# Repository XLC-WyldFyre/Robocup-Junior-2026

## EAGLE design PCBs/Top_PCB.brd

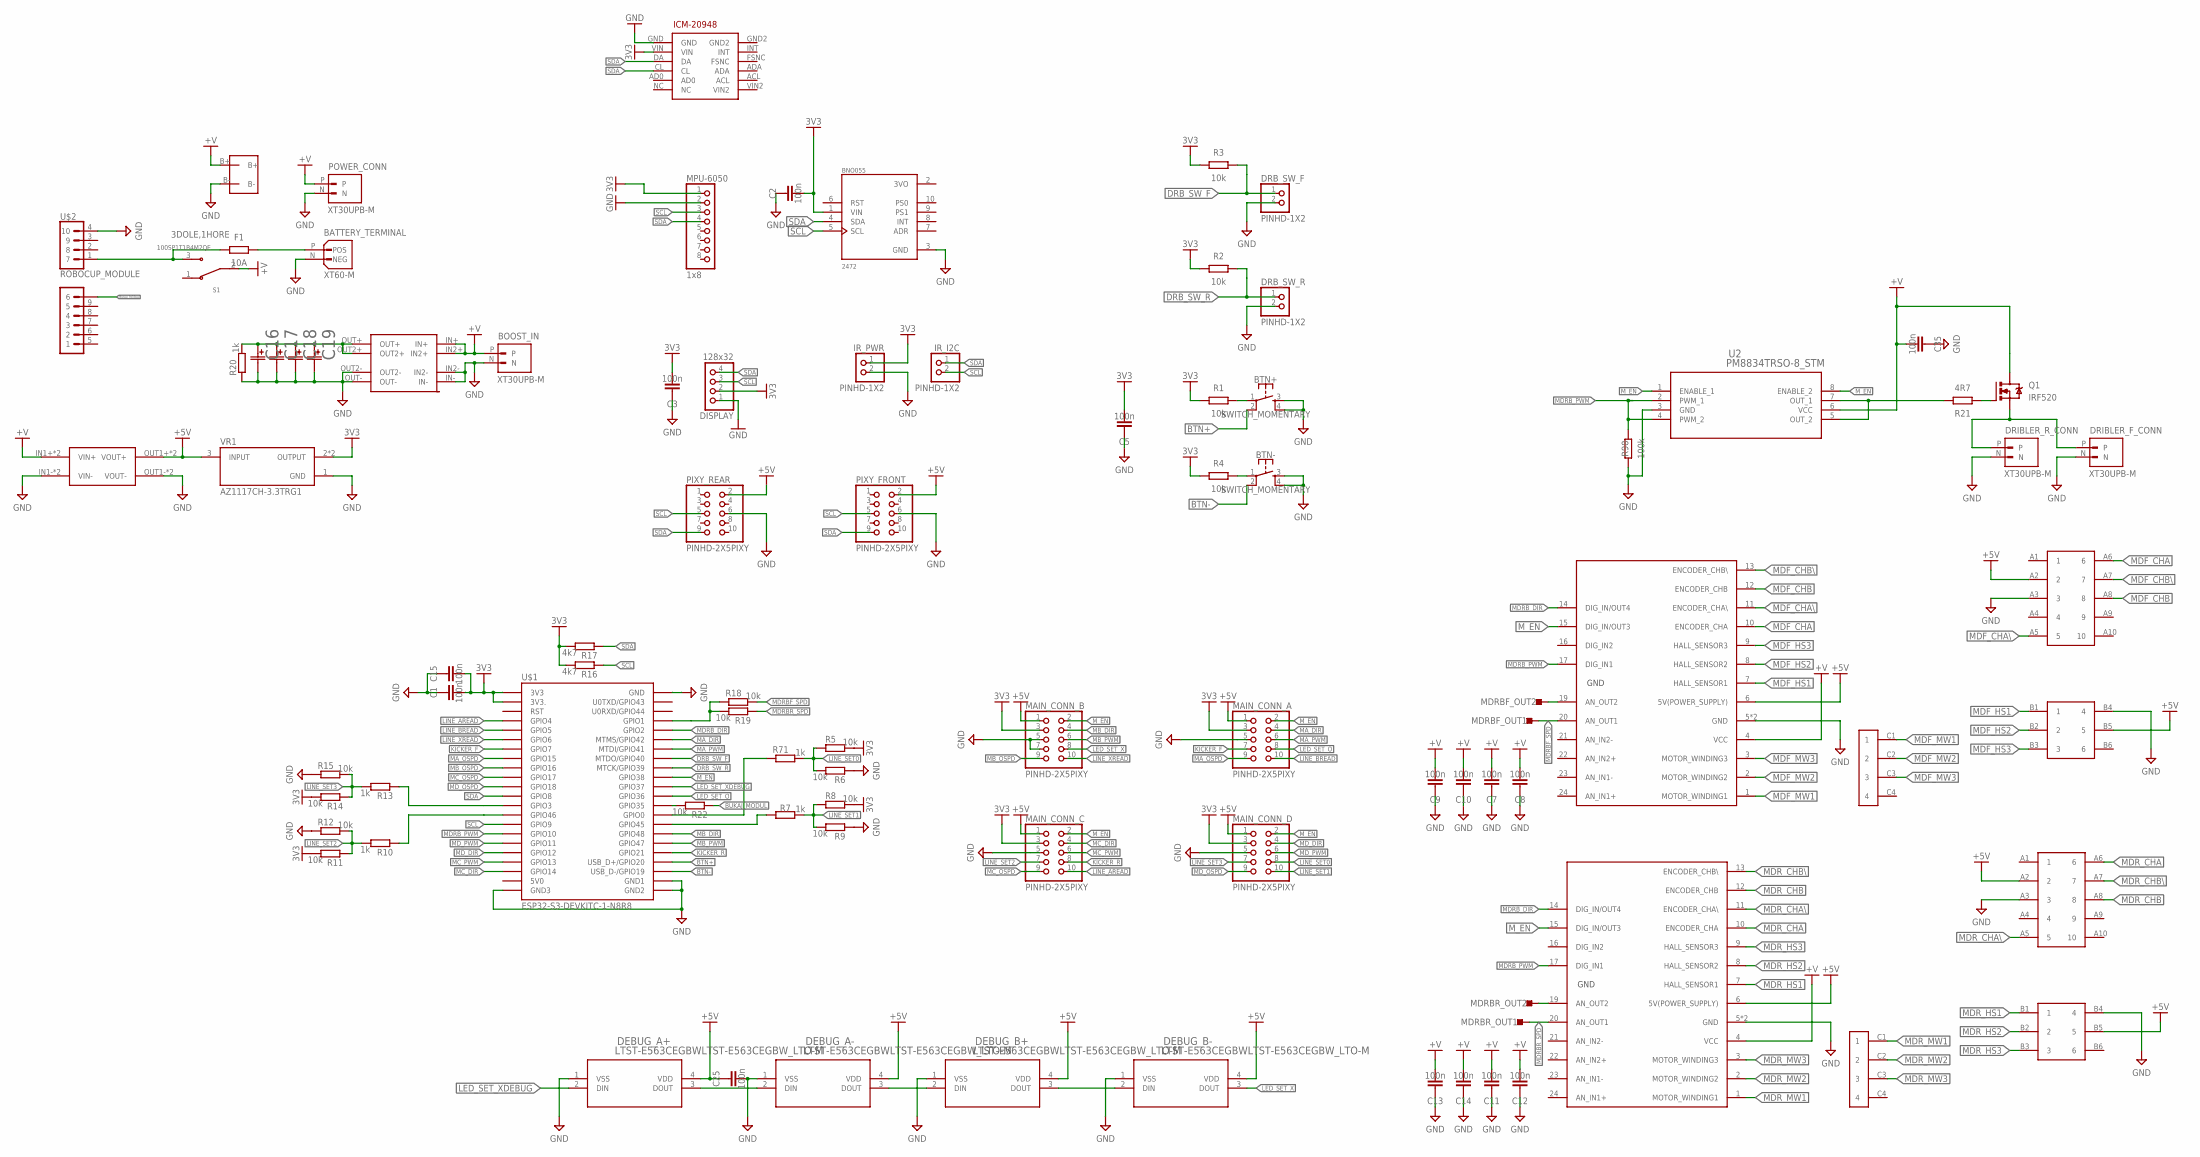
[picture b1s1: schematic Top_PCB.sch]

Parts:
BATTERY_TERMINAL: XT60-M; AMASS_XT60-M
BATT_VOLTAGE: BATT_V_METER; 1X02
BNO055: 2472; MODULE_2472
BOOST_IN: XT30UPB-M; AMASS_XT30UPB-M
BTN+: SWITCH_MOMENTARY; SWITCH-MOMENTARY-PTH-6.5MM
BTN-: SWITCH_MOMENTARY; SWITCH-MOMENTARY-PTH-6.5MM
C1, C2, C3, C5, C7, C8, C9, C10, C11, C12, C13, C14, C15, C25, C35: 100n; CAPC2012X110
C16, C17, C18, C19: 1mF; CAP_108CKE_ILC
DEBUG_A+: LTST-E563CEGBWLTST-E563CEGBW_LTO-M; LTST-E563CEGBW_LTO-M
DEBUG_A-: LTST-E563CEGBWLTST-E563CEGBW_LTO-M; LTST-E563CEGBW_LTO-M
DEBUG_B+: LTST-E563CEGBWLTST-E563CEGBW_LTO-M; LTST-E563CEGBW_LTO-M
DEBUG_B-: LTST-E563CEGBWLTST-E563CEGBW_LTO-M; LTST-E563CEGBW_LTO-M
DISPLAY: 128x32; 1X04
DRB_SW_F: PINHD-1X2; 1X02
DRB_SW_R: PINHD-1X2; 1X02
DRIBLER_F_CONN: XT30UPB-M; AMASS_XT30UPB-M
DRIBLER_R_CONN: XT30UPB-M; AMASS_XT30UPB-M
F1: 10A; RESC3216X70
ICM-20948: ICM-20948
IR_I2C: PINHD-1X2; 1X02
IR_PWR: PINHD-1X2; 1X02
MAIN_CONN_A: PINHD-2X5PIXY; 2X05
MAIN_CONN_B: PINHD-2X5PIXY; 2X05
MAIN_CONN_C: PINHD-2X5PIXY; 2X05
MAIN_CONN_D: PINHD-2X5PIXY; 2X05
MDRBF_OUT1, MDRBF_OUT2: TESTPOINT_TPS-PAD-036; TESTPOINT_PAD-036
MDRBR_OUT1, MDRBR_OUT2: TESTPOINT_TPS-PAD-036; TESTPOINT_PAD-036
MPU-6050: 1x8; 1X08
PIXY_FRONT: PINHD-2X5PIXY; 2X05
PIXY_REAR: PINHD-2X5PIXY; 2X05
POWER_CONN: XT30UPB-M; AMASS_XT30UPB-M
Q1: IRF520; TO220BV
R1, R2, R3, R4, R5, R6, R8, R9, R11, R12, R14, R15, R18, R19, R22: 10k; RESC2012X65
R7, R10, R13, R20, R71: 1k; RESC2012X65
R16, R17: 4k7; RESC2012X65
R21: 4R7; RESC2012X65
R98: 100k; RESC2012X65
S1: 100SP1T1B4M2QE; SW_100SP1T1B4M2QE
U2: PM8834TRSO-8_STM; SO-8_STM
U$1: ESP32-S3-DEVKITC-1-N8R8
U$2: ROBOCUP_MODULE
U$4: MP1584; DC-BRICK
U$5: BOOST
U$7, U$9: ESCON24/224/2; ESCON24/2
U$8, U$11: PIN2.54-2X5
U$10, U$12: MX-44914-0601
U$13, U$14: MX5566
VR1: AZ1117CH-3.3TRG1; VREG_AZ1117CH-3.3TRG1

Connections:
3DOLE,1HORE: F1.1, S1.3, U$2.1 (7)
3V3: BNO055.1 (VIN), C1.2, C2.2, C3.2, C5.2, C15.2, DISPLAY.2, ICM-20948.VIN, IR_PWR.1, MAIN_CONN_A.3, MAIN_CONN_B.3, MAIN_CONN_C.3, MAIN_CONN_D.3, MPU-6050.1, R1.1, R2.1, R3.1, R4.1, R5.1, R8.1, R11.1, R14.1, R16.1, R17.1, U$1.J1_1 (3V3), U$1.J1_2 (3V3.), VR1.2 (OUTPUT), VR1.4 (OUTPUT)
3VO: BNO055.2 (3VO)
5V0: U$1.J1_21 (5V0)
+5V: C25.1, DEBUG_A+.4 (VDD), DEBUG_A-.4 (VDD), DEBUG_B+.4 (VDD), DEBUG_B-.4 (VDD), MAIN_CONN_A.1, MAIN_CONN_B.1, MAIN_CONN_C.1, MAIN_CONN_D.1, PIXY_FRONT.2, PIXY_REAR.2, U$4.OUT1+ (VOUT+), U$4.OUT2+ (VOUT+), U$7.6 (5V(POWER_SUPPLY)), U$8.A2 (2), U$9.6 (5V(POWER_SUPPLY)), U$10.B5 (5), U$11.A2 (2), U$12.B5 (5), VR1.3 (INPUT)
+V: BATT_VOLTAGE.B+, BOOST_IN.P, C7.2, C8.2, C9.2, C10.2, C11.2, C12.2, C13.2, C14.2, C35.2, POWER_CONN.P, Q1.D, S1.2, U2.6 (VCC), U$4.IN1+ (VIN+), U$4.IN2+ (VIN+), U$5.IN2+, U$5.IN+, U$7.4 (VCC), U$9.4 (VCC)
BTN+: BTN+.2, U$1.J3_19 (USB_D+/GPIO20)
BTN-: BTN-.2, U$1.J3_20 (USB_D-/GPIO19)
BUKAJ_MODUL: R22.2, U$2.10 (6)
DRB_SW_F: DRB_SW_F.1, R3.2, U$1.J3_8 (MTDO/GPIO40)
DRB_SW_R: DRB_SW_R.1, R2.2, U$1.J3_9 (MTCK/GPIO39)
GND: BATTERY_TERMINAL.N (NEG), BATT_VOLTAGE.B-, BNO055.3 (GND), BOOST_IN.N, BTN+.3, BTN+.4, BTN-.3, BTN-.4, C1.1, C2.1, C3.1, C5.1, C7.1, C8.1, C9.1, C10.1, C11.1, C12.1, C13.1, C14.1, C15.1, C16.2, C17.2, C18.2, C19.2, C25.2, C35.1, DEBUG_A+.1 (VSS), DEBUG_A-.1 (VSS), DEBUG_B+.1 (VSS), DEBUG_B-.1 (VSS), DISPLAY.1, DRB_SW_F.2, DRB_SW_R.2, DRIBLER_F_CONN.N, DRIBLER_R_CONN.N, ICM-20948.GND, IR_PWR.2, MAIN_CONN_A.5, MAIN_CONN_B.5, MAIN_CONN_B.7, MAIN_CONN_C.5, MAIN_CONN_D.5, MPU-6050.2, PIXY_FRONT.6, PIXY_REAR.6, POWER_CONN.N, R6.2, R9.2, R12.2, R15.2, R20.2, R98.1, U2.3 (GND), U$1.J1_22 (GND3), U$1.J3_1 (GND), U$1.J3_21 (GND1), U$1.J3_22 (GND2), U$2.4 (10), U$4.IN1- (VIN-), U$4.IN2- (VIN-), U$4.OUT1- (VOUT-), U$4.OUT2- (VOUT-), U$5.IN2-, U$5.IN-, U$5.OUT2-, U$5.OUT-, U$7.5 (GND), U$7.18 (GND), U$8.A3 (3), U$9.5 (GND), U$9.18 (GND), U$10.B4 (4), U$11.A3 (3), U$12.B4 (4), VR1.1 (GND)
KICKER_F: MAIN_CONN_A.7, U$1.J1_7 (GPIO7)
KICKER_R: MAIN_CONN_C.8, U$1.J3_18 (GPIO21)
LED_SET_DEBUG1: DEBUG_A-.3 (DOUT), DEBUG_B+.2 (DIN)
LED_SET_O: MAIN_CONN_A.8, U$1.J3_12 (GPIO36)
LED_SET_X: DEBUG_B-.3 (DOUT), MAIN_CONN_B.8
LED_SET_XDEBUG: DEBUG_A+.2 (DIN), U$1.J3_11 (GPIO37)
LINE_AREAD: MAIN_CONN_C.10, U$1.J1_4 (GPIO4)
LINE_BREAD: MAIN_CONN_A.10, U$1.J1_5 (GPIO5)
LINE_SET0: MAIN_CONN_D.8, R5.2, R6.1, R71.1
LINE_SET1: MAIN_CONN_D.10, R7.1, R8.2, R9.1
LINE_SET2: MAIN_CONN_C.7, R10.1, R11.2, R12.1
LINE_SET3: MAIN_CONN_D.7, R13.1, R14.2, R15.1
LINE_XREAD: MAIN_CONN_B.10, U$1.J1_6 (GPIO6)
MA_DIR: MAIN_CONN_A.4, U$1.J3_6 (MTMS/GPIO42)
MA_OSPD: MAIN_CONN_A.9, U$1.J1_8 (GPIO15)
MA_PWM: MAIN_CONN_A.6, U$1.J3_7 (MTDI/GPIO41)
MB_DIR: MAIN_CONN_B.4, U$1.J3_16 (GPIO48)
MB_OSPD: MAIN_CONN_B.9, U$1.J1_9 (GPIO16)
MB_PWM: MAIN_CONN_B.6, U$1.J3_17 (GPIO47)
MC_DIR: MAIN_CONN_C.4, U$1.J1_20 (GPIO14)
MC_OSPD: MAIN_CONN_C.9, U$1.J1_10 (GPIO17)
MC_PWM: MAIN_CONN_C.6, U$1.J1_19 (GPIO13)
MDF_CHA: U$9.10 (ENCODER_CHA), U$11.A6 (6)
MDF_CHA\\: U$9.11 (ENCODER_CHA\\), U$11.A5 (5)
MDF_CHB: U$9.12 (ENCODER_CHB), U$11.A8 (8)
MDF_CHB\\: U$9.13 (ENCODER_CHB\\), U$11.A7 (7)
MDF_HS1: U$9.7 (HALL_SENSOR1), U$12.B1 (1)
MDF_HS2: U$9.8 (HALL_SENSOR2), U$12.B2 (2)
MDF_HS3: U$9.9 (HALL_SENSOR3), U$12.B3 (3)
MDF_MW1: U$9.1 (MOTOR_WINDING1), U$13.C1 (1)
MDF_MW2: U$9.2 (MOTOR_WINDING2), U$13.C2 (2)
MDF_MW3: U$9.3 (MOTOR_WINDING3), U$13.C3 (3)
MDRBF_SPD: MDRBF_OUT1.1, R18.1, U$9.20 (AN_OUT1)
MDRBR_SPD: MDRBR_OUT1.1, R19.2, U$7.20 (AN_OUT1)
MDRB_DIR: U$1.J3_5 (GPIO2), U$7.14 (DIG_IN/OUT4), U$9.14 (DIG_IN/OUT4)
MDRB_PWM: R98.2, U2.2 (PWM_1), U2.4 (PWM_2), U$1.J1_16 (GPIO10), U$7.17 (DIG_IN1), U$9.17 (DIG_IN1)
MDRB_SPD: R18.2, R19.1, U$1.J3_4 (GPIO1)
MDR_CHA: U$7.10 (ENCODER_CHA), U$8.A6 (6)
MDR_CHA\\: U$7.11 (ENCODER_CHA\\), U$8.A5 (5)
MDR_CHB: U$7.12 (ENCODER_CHB), U$8.A8 (8)
MDR_CHB\\: U$7.13 (ENCODER_CHB\\), U$8.A7 (7)
MDR_HS1: U$7.7 (HALL_SENSOR1), U$10.B1 (1)
MDR_HS2: U$7.8 (HALL_SENSOR2), U$10.B2 (2)
MDR_HS3: U$7.9 (HALL_SENSOR3), U$10.B3 (3)
MDR_MW1: U$7.1 (MOTOR_WINDING1), U$14.C1 (1)
MDR_MW2: U$7.2 (MOTOR_WINDING2), U$14.C2 (2)
MDR_MW3: U$7.3 (MOTOR_WINDING3), U$14.C3 (3)
MD_DIR: MAIN_CONN_D.4, U$1.J1_18 (GPIO12)
MD_OSPD: MAIN_CONN_D.9, U$1.J1_11 (GPIO18)
MD_PWM: MAIN_CONN_D.6, U$1.J1_17 (GPIO11)
M_EN: MAIN_CONN_A.2, MAIN_CONN_B.2, MAIN_CONN_C.2, MAIN_CONN_D.2, U2.1 (ENABLE_1), U2.8 (ENABLE_2), U$1.J3_10 (GPIO38), U$7.15 (DIG_IN/OUT3), U$9.15 (DIG_IN/OUT3)
unnamed: DEBUG_B+.3 (DOUT), DEBUG_B-.2 (DIN)
unnamed: C16.1, C17.1, C18.1, C19.1, R20.1, U$5.OUT2+, U$5.OUT+
unnamed: BATTERY_TERMINAL.P (POS), F1.2
unnamed: Q1.G, R21.1
unnamed: R22.1, U$1.J3_13 (GPIO35)
unnamed: BTN+.1, R1.2
unnamed: MDRBR_OUT2.1, U$7.19 (AN_OUT2)
unnamed: BTN-.1, R4.2
unnamed: R13.2, U$1.J1_13 (GPIO3)
unnamed: R71.2, U$1.J3_14 (GPIO0)
unnamed: DEBUG_A+.3 (DOUT), DEBUG_A-.2 (DIN)
unnamed: DRIBLER_F_CONN.P, DRIBLER_R_CONN.P, Q1.S
unnamed: R10.2, U$1.J1_14 (GPIO46)
unnamed: R7.2, U$1.J3_15 (GPIO45)
unnamed: R21.2, U2.5 (OUT_2), U2.7 (OUT_1)
unnamed: MDRBF_OUT2.1, U$9.19 (AN_OUT2)
SCL: BNO055.5 (SCL), DISPLAY.3, IR_I2C.2, MPU-6050.3, PIXY_FRONT.5, PIXY_REAR.5, R16.2, U$1.J1_15 (GPIO9)
SDA: BNO055.4 (SDA), DISPLAY.4, ICM-20948.CL, ICM-20948.DA, IR_I2C.1, MPU-6050.4, PIXY_FRONT.9, PIXY_REAR.9, R17.2, U$1.J1_12 (GPIO8)

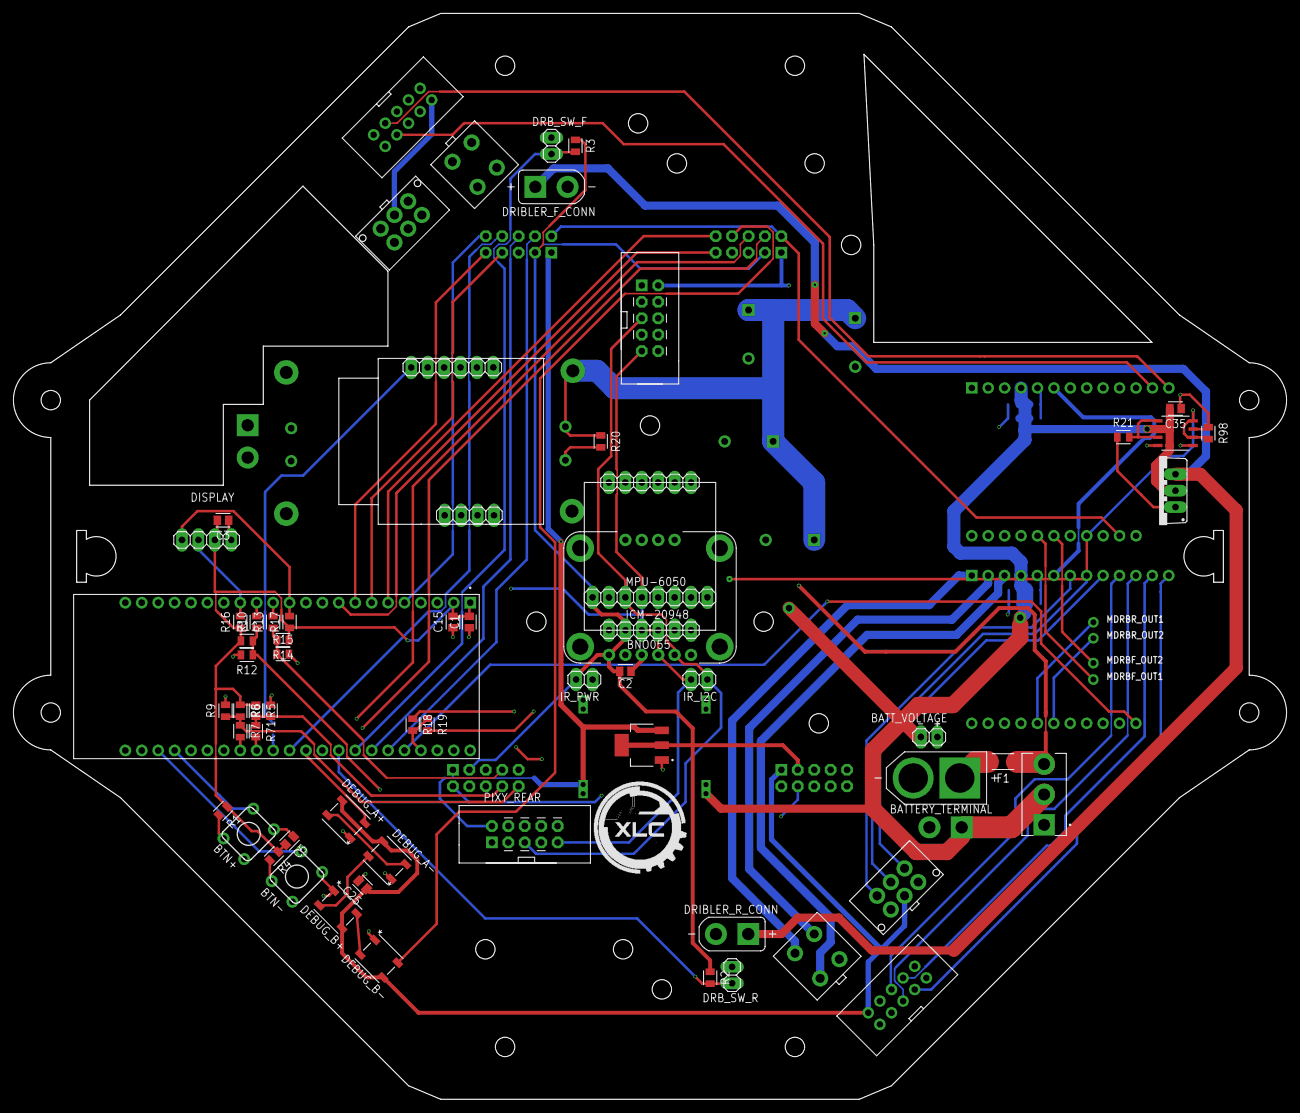
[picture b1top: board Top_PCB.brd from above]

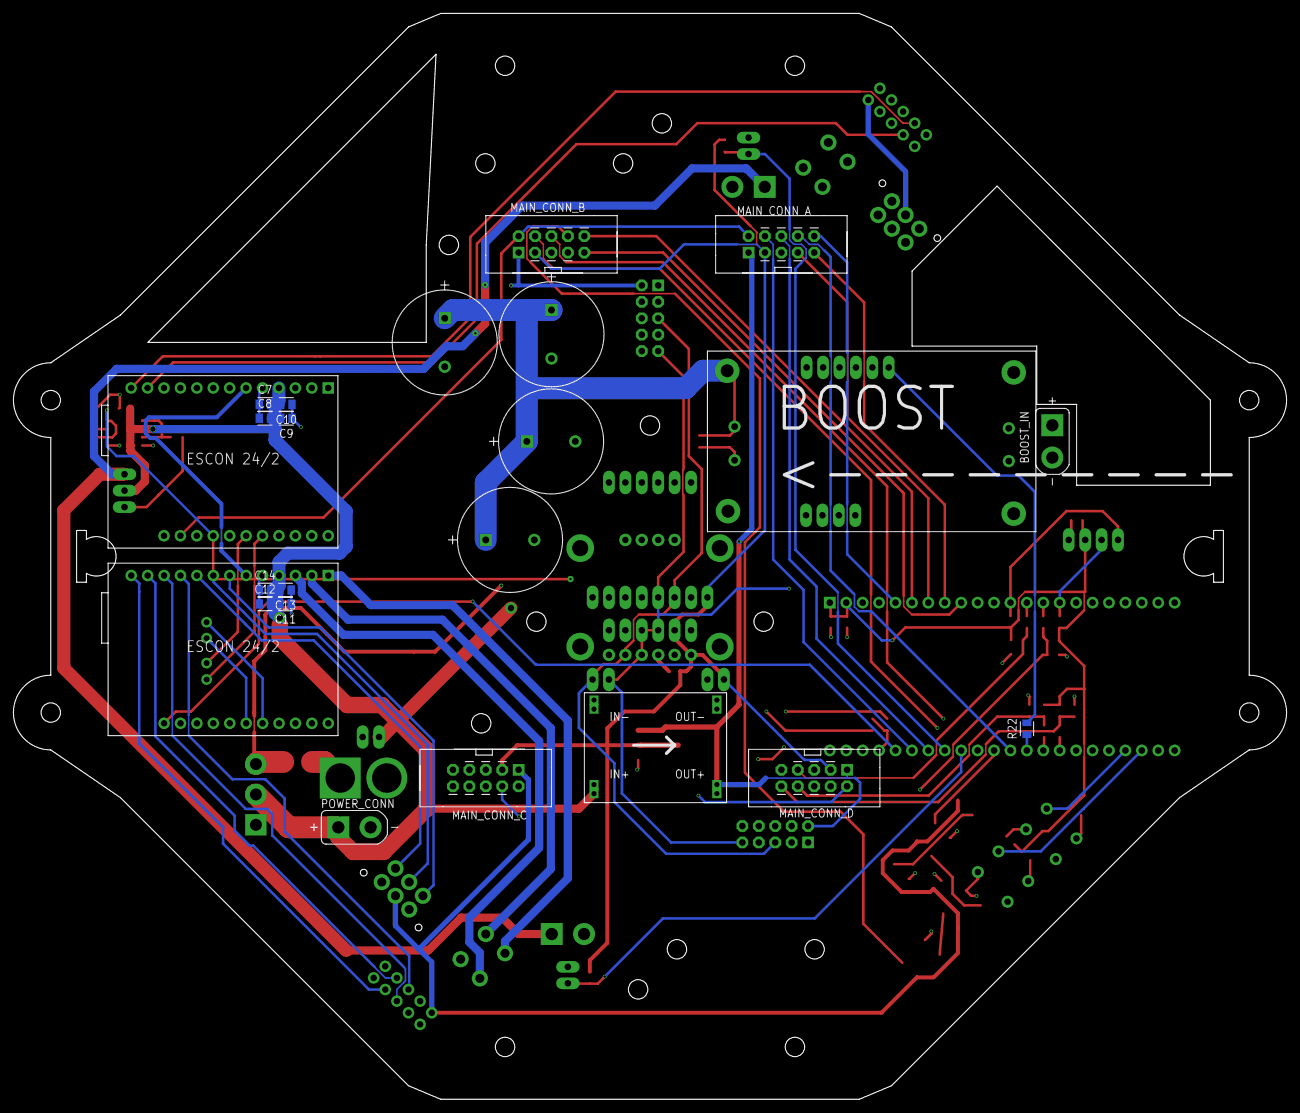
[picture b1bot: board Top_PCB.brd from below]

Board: 4 copper layers, 196.9 x 168.0 mm, 90 parts (23 on the bottom side), 79 nets.

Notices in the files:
parts and their libraries:
COPYRIGHT: Copyright (C) 2025 Ultra Librarian. All rights reserved.
COPYRIGHT: Copyright (C) 2026 Ultra Librarian. All rights reserved.
